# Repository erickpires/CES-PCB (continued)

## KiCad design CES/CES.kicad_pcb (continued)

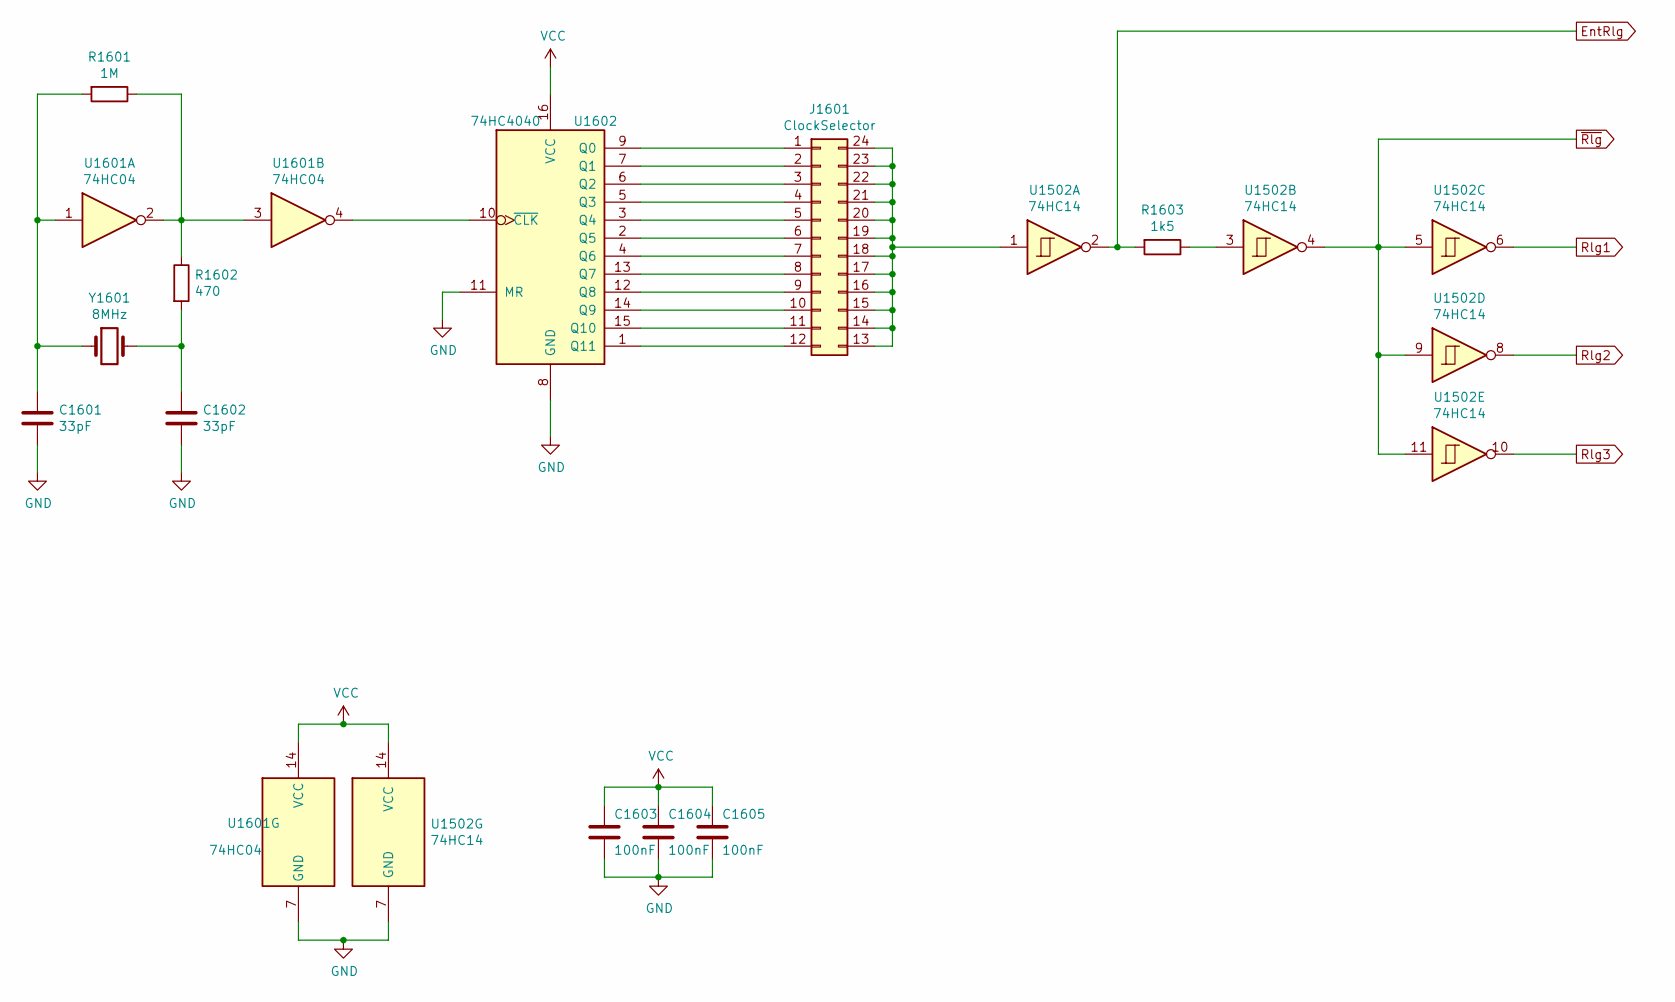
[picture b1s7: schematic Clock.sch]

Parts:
C1601, C1602: 33pF; CP_Radial_D5.0mm_P2.50mm
C1603, C1604, C1605: 100nF; CP_Radial_D5.0mm_P2.50mm
J1601: ClockSelector; PinHeader_2x12_P2.54mm_Vertical
R1601: 1M; R_Axial_DIN0204_L3.6mm_D1.6mm_P1.90mm_Vertical
R1602: 470; R_Axial_DIN0204_L3.6mm_D1.6mm_P1.90mm_Vertical
R1603: 1k5; R_Axial_DIN0204_L3.6mm_D1.6mm_P1.90mm_Vertical
U1502: 74HC14; DIP-14_W7.62mm
U1601: 74HC04; DIP-14_W7.62mm
U1602: 74HC4040; DIP-16_W7.62mm
Y1601: 8MHz; Crystal_HC33-U_Vertical

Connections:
EntRlg: R1603.2, U1502.2; also elsewhere on the board
GND: C1601.2, C1602.2, C1603.2, C1604.2, C1605.2, U1502.7 (GND), U1601.5, U1601.7 (GND), U1601.9, U1601.11, U1601.13, U1602.8 (GND), U1602.11 (MR); also elsewhere on the board
unnamed: C1601.1, R1601.2, U1601.1, Y1601.1
unnamed: C1602.1, R1602.2, Y1601.2
unnamed: J1601.1, U1602.9 (Q0)
unnamed: J1601.2, U1602.7 (Q1)
unnamed: J1601.3, U1602.6 (Q2)
unnamed: J1601.4, U1602.5 (Q3)
unnamed: J1601.5, U1602.3 (Q4)
unnamed: J1601.6, U1602.2 (Q5)
unnamed: J1601.7, U1602.4 (Q6)
unnamed: J1601.8, U1602.13 (Q7)
unnamed: J1601.9, U1602.12 (Q8)
unnamed: J1601.10, U1602.14 (Q9)
unnamed: J1601.11, U1602.15 (Q10)
unnamed: J1601.12, U1602.1 (Q11)
unnamed: J1601.13, J1601.14, J1601.15, J1601.16, J1601.17, J1601.18, J1601.19, J1601.20, J1601.21, J1601.22, J1601.23, J1601.24, U1502.1
unnamed: R1601.1, R1602.1, U1601.2, U1601.3
unnamed: R1603.1, U1502.3
unnamed: U1601.4, U1602.10 (~CLK)
Rlg1: U1502.6; also elsewhere on the board
Rlg2: U1502.8; also elsewhere on the board
Rlg3: U1502.10; also elsewhere on the board
VCC: C1603.1, C1604.1, C1605.1, U1502.14 (VCC), U1601.14 (VCC), U1602.16 (VCC); also elsewhere on the board
~Rlg: U1502.4, U1502.5, U1502.9, U1502.11; also elsewhere on the board

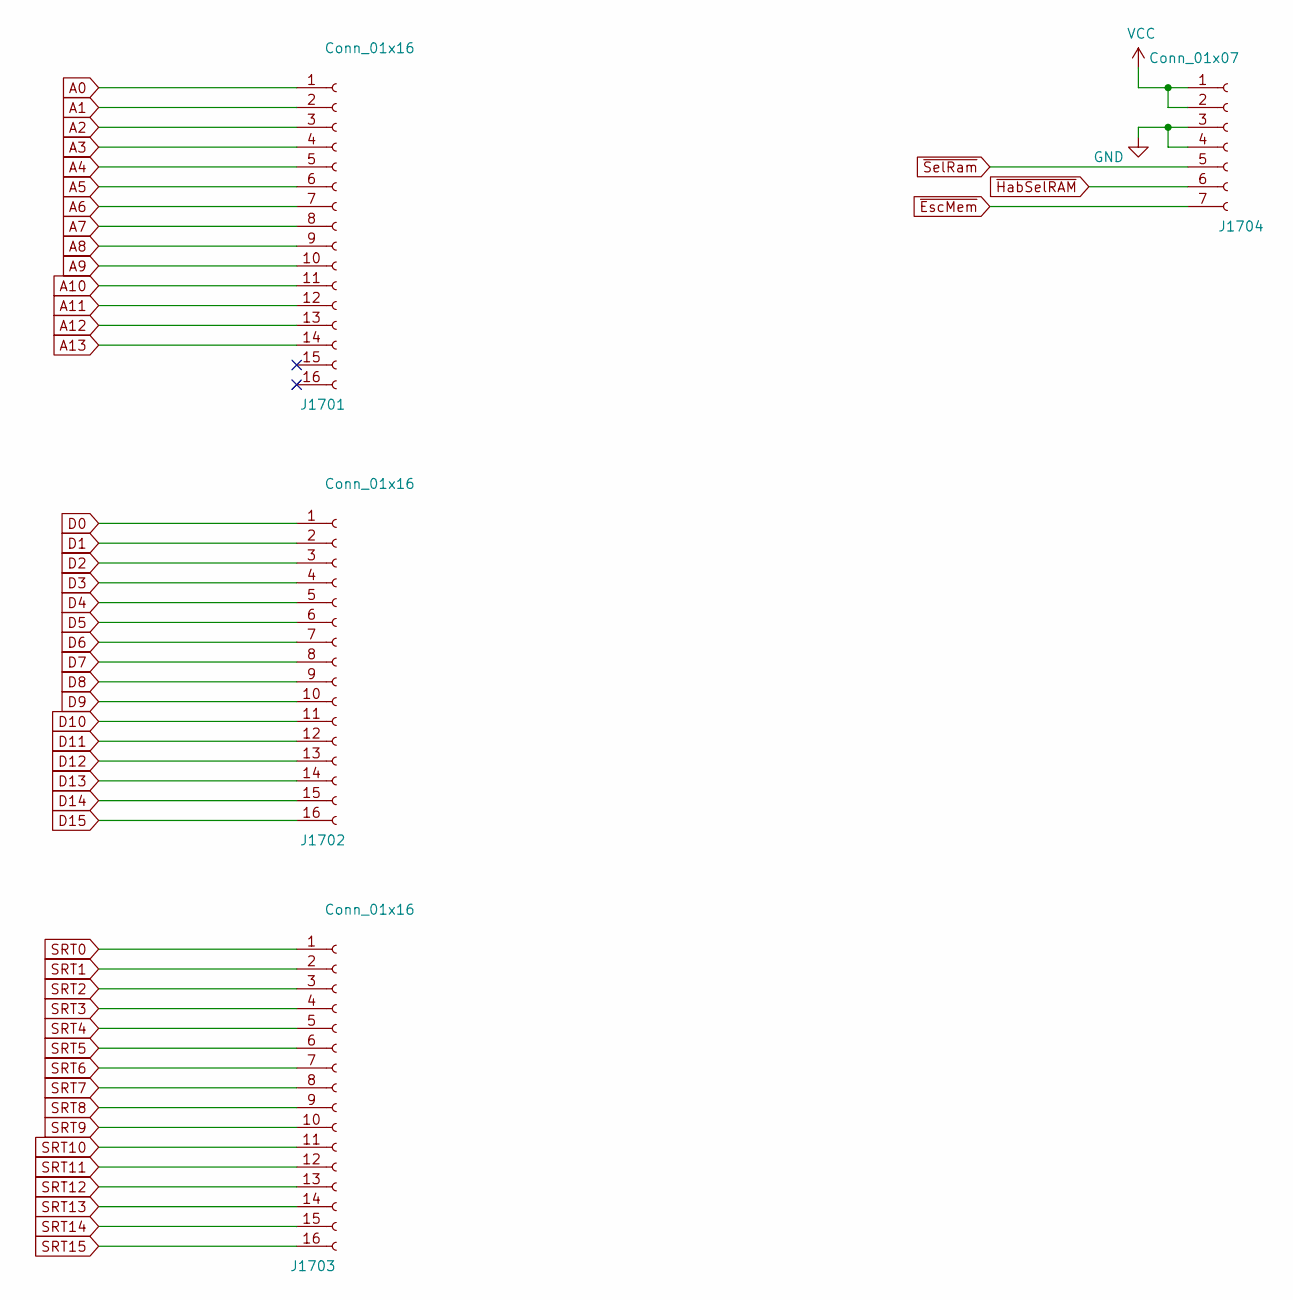
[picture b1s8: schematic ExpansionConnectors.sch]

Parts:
J1701, J1702, J1703: Conn_01x16; PinHeader_1x16_P2.54mm_Vertical
J1704: Conn_01x07; PinHeader_1x07_P2.54mm_Vertical

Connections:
A0: J1701.1; also elsewhere on the board
A1: J1701.2; also elsewhere on the board
A2: J1701.3; also elsewhere on the board
A3: J1701.4; also elsewhere on the board
A4: J1701.5; also elsewhere on the board
A5: J1701.6; also elsewhere on the board
A6: J1701.7; also elsewhere on the board
A7: J1701.8; also elsewhere on the board
A8: J1701.9; also elsewhere on the board
A9: J1701.10; also elsewhere on the board
A10: J1701.11; also elsewhere on the board
A11: J1701.12; also elsewhere on the board
A12: J1701.13; also elsewhere on the board
A13: J1701.14; also elsewhere on the board
D0: J1702.1; also elsewhere on the board
D1: J1702.2; also elsewhere on the board
D2: J1702.3; also elsewhere on the board
D3: J1702.4; also elsewhere on the board
D4: J1702.5; also elsewhere on the board
D5: J1702.6; also elsewhere on the board
D6: J1702.7; also elsewhere on the board
D7: J1702.8; also elsewhere on the board
D8: J1702.9; also elsewhere on the board
D9: J1702.10; also elsewhere on the board
D10: J1702.11; also elsewhere on the board
D11: J1702.12; also elsewhere on the board
D12: J1702.13; also elsewhere on the board
D13: J1702.14; also elsewhere on the board
D14: J1702.15; also elsewhere on the board
D15: J1702.16; also elsewhere on the board
GND: J1704.3, J1704.4; also elsewhere on the board
SRT0: J1703.1; also elsewhere on the board
SRT1: J1703.2; also elsewhere on the board
SRT2: J1703.3; also elsewhere on the board
SRT3: J1703.4; also elsewhere on the board
SRT4: J1703.5; also elsewhere on the board
SRT5: J1703.6; also elsewhere on the board
SRT6: J1703.7; also elsewhere on the board
SRT7: J1703.8; also elsewhere on the board
SRT8: J1703.9; also elsewhere on the board
SRT9: J1703.10; also elsewhere on the board
SRT10: J1703.11; also elsewhere on the board
SRT11: J1703.12; also elsewhere on the board
SRT12: J1703.13; also elsewhere on the board
SRT13: J1703.14; also elsewhere on the board
SRT14: J1703.15; also elsewhere on the board
SRT15: J1703.16; also elsewhere on the board
VCC: J1704.1, J1704.2; also elsewhere on the board
~EscMem: J1704.7; also elsewhere on the board
~HabSelRAM: J1704.6; also elsewhere on the board
~SelRam: J1704.5; also elsewhere on the board

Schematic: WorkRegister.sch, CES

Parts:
C401, C402, C403, C404, C405, C406: 100nF; C_Disc_D4.3mm_W1.9mm_P5.00mm
U401, U402, U403, U404: 74HC173; DIP-16_W7.62mm
U405, U406: 74HC244; DIP-20_W7.62mm

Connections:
GND: C401.2, C402.2, C403.2, C404.2, C405.2, C406.2, U401.1 (Oe1), U401.2 (Oe2), U401.8 (GND), U401.10 (E2), U401.15 (Mr), U402.1 (Oe1), U402.2 (Oe2), U402.8 (GND), U402.10 (E2), U402.15 (Mr), U403.1 (Oe1), U403.2 (Oe2), U403.8 (GND), U403.10 (E2), U403.15 (Mr), U404.1 (Oe1), U404.2 (Oe2), U404.8 (GND), U404.10 (E2), U404.15 (Mr), U405.10 (GND), U406.10 (GND); also elsewhere on the board
Rlg1: U401.7 (Cp), U402.7 (Cp), U403.7 (Cp), U404.7 (Cp); also elsewhere on the board
SRT0: U401.3 (Q0), U405.2 (1A0); also elsewhere on the board
SRT1: U401.4 (Q1), U405.4 (1A1); also elsewhere on the board
SRT2: U401.5 (Q2), U405.6 (1A2); also elsewhere on the board
SRT3: U401.6 (Q3), U405.8 (1A3); also elsewhere on the board
SRT4: U402.3 (Q0), U405.17 (2A0); also elsewhere on the board
SRT5: U402.4 (Q1), U405.15 (2A1); also elsewhere on the board
SRT6: U402.5 (Q2), U405.13 (2A2); also elsewhere on the board
SRT7: U402.6 (Q3), U405.11 (2A3); also elsewhere on the board
SRT8: U403.3 (Q0), U406.2 (1A0); also elsewhere on the board
SRT9: U403.4 (Q1), U406.4 (1A1); also elsewhere on the board
SRT10: U403.5 (Q2), U406.6 (1A2); also elsewhere on the board
SRT11: U403.6 (Q3), U406.8 (1A3); also elsewhere on the board
SRT12: U404.3 (Q0), U406.17 (2A0); also elsewhere on the board
SRT13: U404.4 (Q1), U406.15 (2A1); also elsewhere on the board
SRT14: U404.5 (Q2), U406.13 (2A2); also elsewhere on the board
SRT15: U404.6 (Q3), U406.11 (2A3); also elsewhere on the board
SS0: U401.14 (D0); also elsewhere on the board
SS1: U401.13 (D1); also elsewhere on the board
SS2: U401.12 (D2); also elsewhere on the board
SS3: U401.11 (D3); also elsewhere on the board
SS4: U402.14 (D0); also elsewhere on the board
SS5: U402.13 (D1); also elsewhere on the board
SS6: U402.12 (D2); also elsewhere on the board
SS7: U402.11 (D3); also elsewhere on the board
SS8: U403.14 (D0); also elsewhere on the board
SS9: U403.13 (D1); also elsewhere on the board
SS10: U403.12 (D2); also elsewhere on the board
SS11: U403.11 (D3); also elsewhere on the board
SS12: U404.14 (D0); also elsewhere on the board
SS13: U404.13 (D1); also elsewhere on the board
SS14: U404.12 (D2); also elsewhere on the board
SS15: U404.11 (D3); also elsewhere on the board
VCC: C401.1, C402.1, C403.1, C404.1, C405.1, C406.1, U401.16 (VCC), U402.16 (VCC), U403.16 (VCC), U404.16 (VCC), U405.20 (VCC), U406.20 (VCC); also elsewhere on the board
VDB0: U405.18 (1Y0); also elsewhere on the board
VDB1: U405.16 (1Y1); also elsewhere on the board
VDB2: U405.14 (1Y2); also elsewhere on the board
VDB3: U405.12 (1Y3); also elsewhere on the board
VDB4: U405.3 (2Y0); also elsewhere on the board
VDB5: U405.5 (2Y1); also elsewhere on the board
VDB6: U405.7 (2Y2); also elsewhere on the board
VDB7: U405.9 (2Y3); also elsewhere on the board
VDB8: U406.18 (1Y0); also elsewhere on the board
VDB9: U406.16 (1Y1); also elsewhere on the board
VDB10: U406.14 (1Y2); also elsewhere on the board
VDB11: U406.12 (1Y3); also elsewhere on the board
VDB12: U406.3 (2Y0); also elsewhere on the board
VDB13: U406.5 (2Y1); also elsewhere on the board
VDB14: U406.7 (2Y2); also elsewhere on the board
VDB15: U406.9 (2Y3); also elsewhere on the board
~EscM: U405.1 (1OE), U405.19 (2OE), U406.1 (1OE), U406.19 (2OE); also elsewhere on the board
~EscT: U401.9 (E1), U402.9 (E1), U403.9 (E1), U404.9 (E1); also elsewhere on the board

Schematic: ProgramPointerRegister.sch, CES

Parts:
C501, C502, C503, C504: 100nF; C_Disc_D4.3mm_W1.9mm_P5.00mm
C505: C; C_Disc_D4.3mm_W1.9mm_P5.00mm
R501: R; R_Axial_DIN0204_L3.6mm_D1.6mm_P1.90mm_Vertical
U501, U502, U503, U504: 74HC173; DIP-16_W7.62mm

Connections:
ESA0: U501.3 (Q0); also elsewhere on the board
ESA1: U501.4 (Q1); also elsewhere on the board
ESA2: U501.5 (Q2); also elsewhere on the board
ESA3: U501.6 (Q3); also elsewhere on the board
ESA4: U502.3 (Q0); also elsewhere on the board
ESA5: U502.4 (Q1); also elsewhere on the board
ESA6: U502.5 (Q2); also elsewhere on the board
ESA7: U502.6 (Q3); also elsewhere on the board
ESA8: U503.3 (Q0); also elsewhere on the board
ESA9: U503.4 (Q1); also elsewhere on the board
ESA10: U503.5 (Q2); also elsewhere on the board
ESA11: U503.6 (Q3); also elsewhere on the board
ESA12: U504.3 (Q0); also elsewhere on the board
ESA13: U504.4 (Q1); also elsewhere on the board
ESA14: U504.5 (Q2); also elsewhere on the board
ESA15: U504.6 (Q3); also elsewhere on the board
GND: C501.2, C502.2, C503.2, C504.2, R501.2, U501.2 (Oe2), U501.8 (GND), U501.10 (E2), U502.2 (Oe2), U502.8 (GND), U502.10 (E2), U503.2 (Oe2), U503.8 (GND), U503.10 (E2), U504.2 (Oe2), U504.8 (GND), U504.10 (E2); also elsewhere on the board
unnamed: C505.2, R501.1, U501.15 (Mr), U502.15 (Mr), U503.15 (Mr), U504.15 (Mr)
Rlg1: U501.7 (Cp), U502.7 (Cp), U503.7 (Cp), U504.7 (Cp); also elsewhere on the board
SS0: U501.14 (D0); also elsewhere on the board
SS1: U501.13 (D1); also elsewhere on the board
SS2: U501.12 (D2); also elsewhere on the board
SS3: U501.11 (D3); also elsewhere on the board
SS4: U502.14 (D0); also elsewhere on the board
SS5: U502.13 (D1); also elsewhere on the board
SS6: U502.12 (D2); also elsewhere on the board
SS7: U502.11 (D3); also elsewhere on the board
SS8: U503.14 (D0); also elsewhere on the board
SS9: U503.13 (D1); also elsewhere on the board
SS10: U503.12 (D2); also elsewhere on the board
SS11: U503.11 (D3); also elsewhere on the board
SS12: U504.14 (D0); also elsewhere on the board
SS13: U504.13 (D1); also elsewhere on the board
SS14: U504.12 (D2); also elsewhere on the board
SS15: U504.11 (D3); also elsewhere on the board
VCC: C501.1, C502.1, C503.1, C504.1, C505.1, U501.16 (VCC), U502.16 (VCC), U503.16 (VCC), U504.16 (VCC); also elsewhere on the board
~EscP: U501.9 (E1), U502.9 (E1), U503.9 (E1), U504.9 (E1); also elsewhere on the board
~SaiRP: U501.1 (Oe1), U502.1 (Oe1), U503.1 (Oe1), U504.1 (Oe1); also elsewhere on the board

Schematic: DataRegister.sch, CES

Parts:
C601, C602, C603, C604: 100nF; CP_Radial_D5.0mm_P2.50mm
U601: RD1; DIP-16_W7.62mm
U602: RD2; DIP-16_W7.62mm
U603: RD3; DIP-16_W7.62mm
U604: RD4; DIP-16_W7.62mm

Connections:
ESA0: U601.3 (Q0); also elsewhere on the board
ESA1: U601.4 (Q1); also elsewhere on the board
ESA2: U601.5 (Q2); also elsewhere on the board
ESA3: U601.6 (Q3); also elsewhere on the board
ESA4: U602.3 (Q0); also elsewhere on the board
ESA5: U602.4 (Q1); also elsewhere on the board
ESA6: U602.5 (Q2); also elsewhere on the board
ESA7: U602.6 (Q3); also elsewhere on the board
ESA8: U603.3 (Q0); also elsewhere on the board
ESA9: U603.4 (Q1); also elsewhere on the board
ESA10: U603.5 (Q2); also elsewhere on the board
ESA11: U603.6 (Q3); also elsewhere on the board
ESA12: U604.3 (Q0); also elsewhere on the board
ESA13: U604.4 (Q1); also elsewhere on the board
ESA14: U604.5 (Q2); also elsewhere on the board
ESA15: U604.6 (Q3); also elsewhere on the board
GND: C601.2, C602.2, C603.2, C604.2, U601.2 (Oe2), U601.8 (GND), U601.9 (E1), U601.10 (E2), U601.15 (Mr), U602.2 (Oe2), U602.8 (GND), U602.9 (E1), U602.10 (E2), U602.15 (Mr), U603.2 (Oe2), U603.8 (GND), U603.9 (E1), U603.10 (E2), U603.15 (Mr), U604.2 (Oe2), U604.8 (GND), U604.9 (E1), U604.10 (E2), U604.15 (Mr); also elsewhere on the board
Rlg2: U601.7 (Cp), U602.7 (Cp), U603.7 (Cp), U604.7 (Cp); also elsewhere on the board
VCC: C601.1, C602.1, C603.1, C604.1, U601.16 (VCC), U602.16 (VCC), U603.16 (VCC), U604.16 (VCC); also elsewhere on the board
VDB0: U601.14 (D0); also elsewhere on the board
VDB1: U601.13 (D1); also elsewhere on the board
VDB2: U601.12 (D2); also elsewhere on the board
VDB3: U601.11 (D3); also elsewhere on the board
VDB4: U602.14 (D0); also elsewhere on the board
VDB5: U602.13 (D1); also elsewhere on the board
VDB6: U602.12 (D2); also elsewhere on the board
VDB7: U602.11 (D3); also elsewhere on the board
VDB8: U603.14 (D0); also elsewhere on the board
VDB9: U603.13 (D1); also elsewhere on the board
VDB10: U603.12 (D2); also elsewhere on the board
VDB11: U603.11 (D3); also elsewhere on the board
VDB12: U604.14 (D0); also elsewhere on the board
VDB13: U604.13 (D1); also elsewhere on the board
VDB14: U604.12 (D2); also elsewhere on the board
VDB15: U604.11 (D3); also elsewhere on the board
~UltC: U601.1 (Oe1), U602.1 (Oe1), U603.1 (Oe1), U604.1 (Oe1); also elsewhere on the board

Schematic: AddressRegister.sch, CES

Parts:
C701, C702, C703, C704: 100nF; CP_Radial_D5.0mm_P2.50mm
U701: RE1; DIP-16_W7.62mm
U702: RE2; DIP-16_W7.62mm
U703: RE3; DIP-16_W7.62mm
U704: RE4; DIP-16_W7.62mm

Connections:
GND: C701.2, C702.2, C703.2, C704.2, U701.2 (Oe2), U701.8 (GND), U701.9 (E1), U701.10 (E2), U701.15 (Mr), U702.2 (Oe2), U702.8 (GND), U702.9 (E1), U702.10 (E2), U702.15 (Mr), U703.2 (Oe2), U703.8 (GND), U703.9 (E1), U703.10 (E2), U703.15 (Mr), U704.2 (Oe2), U704.8 (GND), U704.9 (E1), U704.10 (E2), U704.11 (D3), U704.12 (D2), U704.15 (Mr); also elsewhere on the board
Rlg2: U701.7 (Cp), U702.7 (Cp), U703.7 (Cp), U704.7 (Cp); also elsewhere on the board
SME0: U701.14 (D0); also elsewhere on the board
SME1: U701.13 (D1); also elsewhere on the board
SME2: U701.12 (D2); also elsewhere on the board
SME3: U701.11 (D3); also elsewhere on the board
SME4: U702.14 (D0); also elsewhere on the board
SME5: U702.13 (D1); also elsewhere on the board
SME6: U702.12 (D2); also elsewhere on the board
SME7: U702.11 (D3); also elsewhere on the board
SME8: U703.14 (D0); also elsewhere on the board
SME9: U703.13 (D1); also elsewhere on the board
SME10: U703.12 (D2); also elsewhere on the board
SME11: U703.11 (D3); also elsewhere on the board
SME12: U704.14 (D0); also elsewhere on the board
SME13: U704.13 (D1); also elsewhere on the board
VCC: C701.1, C702.1, C703.1, C704.1, U701.16 (VCC), U702.16 (VCC), U703.16 (VCC), U704.16 (VCC); also elsewhere on the board
VEB0: U701.3 (Q0); also elsewhere on the board
VEB1: U701.4 (Q1); also elsewhere on the board
VEB2: U701.5 (Q2); also elsewhere on the board
VEB3: U701.6 (Q3); also elsewhere on the board
VEB4: U702.3 (Q0); also elsewhere on the board
VEB5: U702.4 (Q1); also elsewhere on the board
VEB6: U702.5 (Q2); also elsewhere on the board
VEB7: U702.6 (Q3); also elsewhere on the board
VEB8: U703.3 (Q0); also elsewhere on the board
VEB9: U703.4 (Q1); also elsewhere on the board
VEB10: U703.5 (Q2); also elsewhere on the board
VEB11: U703.6 (Q3); also elsewhere on the board
VEB12: U704.3 (Q0); also elsewhere on the board
VEB13: U704.4 (Q1); also elsewhere on the board
~SaiRE: U701.1 (Oe1), U702.1 (Oe1), U703.1 (Oe1), U704.1 (Oe1); also elsewhere on the board

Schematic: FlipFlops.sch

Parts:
C901, C902, C903, C904: 100nF; C_Disc_D4.3mm_W1.9mm_P5.00mm
U901, U904: 74HC74; DIP-14_W7.62mm
U902: 74HC175; DIP-16_W7.62mm
U903: 74HC112; DIP-16_W7.62mm

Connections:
BotC0: U901.1 (~R); also elsewhere on the board
BotC1: U901.4 (~S); also elsewhere on the board
BotEscMem: U902.11 (~Q2); also elsewhere on the board
BotMem: U902.12 (D2); also elsewhere on the board
BotMudaP: U902.5 (D1); also elsewhere on the board
BotMudaT: U902.4 (D0); also elsewhere on the board
Est1: U901.9 (Q); also elsewhere on the board
GND: C901.2, C902.2, C903.2, C904.2, U901.7 (GND), U902.8 (GND), U903.8 (GND), U904.7 (GND); also elsewhere on the board
I0: U904.5 (Q); also elsewhere on the board
I1: U904.9 (Q); also elsewhere on the board
MudaP: U902.6 (~Q1); also elsewhere on the board
MudaT: U902.3 (~Q0); also elsewhere on the board
Para: U903.5 (Q); also elsewhere on the board
Parte: U902.15 (Q3), U903.2 (K), U903.11 (J); also elsewhere on the board
RC: U901.5 (Q); also elsewhere on the board
Rlg3: U901.11 (C), U902.9 (Cp); also elsewhere on the board
RlgRC: U901.3 (C); also elsewhere on the board
RlgRI: U904.3 (C), U904.11 (C); also elsewhere on the board
VCC: C901.1, C902.1, C903.1, C904.1, U901.10 (~S), U901.13 (~R), U901.14 (VCC), U902.1 (~Mr), U902.16 (VCC), U903.4 (~S), U903.10 (~S), U903.14 (~R), U903.15 (~R), U903.16 (VCC), U904.1 (~R), U904.4 (~S), U904.10 (~S), U904.13 (~R), U904.14 (VCC); also elsewhere on the board
VDB14: U904.2 (D); also elsewhere on the board
VDB15: U904.12 (D); also elsewhere on the board
VaiParar: U903.3 (J); also elsewhere on the board
VaiPartir: U902.13 (D3); also elsewhere on the board
VaiUm: U901.2 (D); also elsewhere on the board
~BotEscMem: U902.10 (Q2); also elsewhere on the board
~BotParteAtivo: U903.12 (K); also elsewhere on the board
~Est1: U901.8 (~Q); also elsewhere on the board
~I0: U904.6 (~Q); also elsewhere on the board
~I1: U904.8 (~Q); also elsewhere on the board
~Para: U903.6 (~Q); also elsewhere on the board
~Parte: U902.14 (~Q3); also elsewhere on the board
~Partiu: U903.7 (~Q); also elsewhere on the board
~RC: U901.6 (~Q); also elsewhere on the board
~Rlg: U903.1 (C), U903.13 (C); also elsewhere on the board
~UltC: U901.12 (D); also elsewhere on the board

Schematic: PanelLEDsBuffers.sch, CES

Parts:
C1301, C1302, C1303, C1304, C1305, C1306, C1307, C1308: 100nF; CP_Radial_D5.0mm_P2.50mm
J1301: PanelRT; PinHeader_1x16_P2.54mm_Vertical
J1302: PanelMem; PinHeader_1x16_P2.54mm_Vertical
J1303: PanelEnd; PinHeader_1x16_P2.54mm_Vertical
U1301, U1302, U1303, U1304, U1305, U1306, U1307, U1308: 74HC04; DIP-14_W7.62mm

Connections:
GND: C1301.2, C1302.2, C1303.2, C1304.2, C1305.2, C1306.2, C1307.2, C1308.2, U1301.7 (GND), U1302.7 (GND), U1303.7 (GND), U1304.7 (GND), U1305.7 (GND), U1306.7 (GND), U1307.7 (GND), U1308.7 (GND); also elsewhere on the board
unnamed: J1301.1, U1301.2
unnamed: J1301.2, U1301.4
unnamed: J1301.3, U1301.6
unnamed: J1301.4, U1301.8
unnamed: J1301.5, U1301.10
unnamed: J1301.6, U1301.12
unnamed: J1301.7, U1302.2
unnamed: J1301.8, U1302.4
unnamed: J1301.9, U1302.6
unnamed: J1301.10, U1302.8
unnamed: J1301.11, U1302.10
unnamed: J1301.12, U1302.12
unnamed: J1301.13, U1303.2
unnamed: J1301.14, U1303.4
unnamed: J1301.15, U1303.6
unnamed: J1301.16, U1303.8
unnamed: J1302.1, U1303.10
unnamed: J1302.2, U1303.12
unnamed: J1302.3, U1304.2
unnamed: J1302.4, U1304.4
unnamed: J1302.5, U1304.6
unnamed: J1302.6, U1304.8
unnamed: J1302.7, U1304.10
unnamed: J1302.8, U1304.12
unnamed: J1302.9, U1305.2
unnamed: J1302.10, U1305.4
unnamed: J1302.11, U1305.6
unnamed: J1302.12, U1305.8
unnamed: J1302.13, U1305.10
unnamed: J1302.14, U1305.12
unnamed: J1302.15, U1306.2
unnamed: J1302.16, U1306.4
unnamed: J1303.1, U1306.6
unnamed: J1303.2, U1306.8
unnamed: J1303.3, U1306.10
unnamed: J1303.4, U1306.12
unnamed: J1303.5, U1307.2
unnamed: J1303.6, U1307.4
unnamed: J1303.7, U1307.6
unnamed: J1303.8, U1307.8
unnamed: J1303.9, U1307.10
unnamed: J1303.10, U1307.12
unnamed: J1303.11, U1308.2
unnamed: J1303.12, U1308.4
unnamed: J1303.13, U1308.6
unnamed: J1303.14, U1308.8
unnamed: J1303.15, U1308.10
unnamed: J1303.16, U1308.12
Para: U1308.13; also elsewhere on the board
SRT0: U1301.1; also elsewhere on the board
SRT1: U1301.3; also elsewhere on the board
SRT2: U1301.5; also elsewhere on the board
SRT3: U1301.9; also elsewhere on the board
SRT4: U1301.11; also elsewhere on the board
SRT5: U1301.13; also elsewhere on the board
SRT6: U1302.1; also elsewhere on the board
SRT7: U1302.3; also elsewhere on the board
SRT8: U1302.5; also elsewhere on the board
SRT9: U1302.9; also elsewhere on the board
SRT10: U1302.11; also elsewhere on the board
SRT11: U1302.13; also elsewhere on the board
SRT12: U1303.1; also elsewhere on the board
SRT13: U1303.3; also elsewhere on the board
SRT14: U1303.5; also elsewhere on the board
SRT15: U1303.9; also elsewhere on the board
SS0: U1306.5; also elsewhere on the board
SS1: U1306.9; also elsewhere on the board
SS2: U1306.11; also elsewhere on the board
SS3: U1306.13; also elsewhere on the board
SS4: U1307.1; also elsewhere on the board
SS5: U1307.3; also elsewhere on the board
SS6: U1307.5; also elsewhere on the board
SS7: U1307.9; also elsewhere on the board
SS8: U1307.11; also elsewhere on the board
SS9: U1307.13; also elsewhere on the board
SS10: U1308.1; also elsewhere on the board
SS11: U1308.3; also elsewhere on the board
SS12: U1308.5; also elsewhere on the board
SS13: U1308.9; also elsewhere on the board
VCC: C1301.1, C1302.1, C1303.1, C1304.1, C1305.1, C1306.1, C1307.1, C1308.1, U1301.14 (VCC), U1302.14 (VCC), U1303.14 (VCC), U1304.14 (VCC), U1305.14 (VCC), U1306.14 (VCC), U1307.14 (VCC), U1308.14 (VCC); also elsewhere on the board
VDB0: U1303.11; also elsewhere on the board
VDB1: U1303.13; also elsewhere on the board
VDB2: U1304.1; also elsewhere on the board
VDB3: U1304.3; also elsewhere on the board
VDB4: U1304.5; also elsewhere on the board
VDB5: U1304.9; also elsewhere on the board
VDB6: U1304.11; also elsewhere on the board
VDB7: U1304.13; also elsewhere on the board
VDB8: U1305.1; also elsewhere on the board
VDB9: U1305.3; also elsewhere on the board
VDB10: U1305.5; also elsewhere on the board
VDB11: U1305.9; also elsewhere on the board
VDB12: U1305.11; also elsewhere on the board
VDB13: U1305.13; also elsewhere on the board
VDB14: U1306.1; also elsewhere on the board
VDB15: U1306.3; also elsewhere on the board
~RC: U1308.11; also elsewhere on the board

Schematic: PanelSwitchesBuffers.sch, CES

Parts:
C1401, C1402, C1403, C1404, C1405, C1406: 100nF; CP_Radial_D5.0mm_P2.50mm
J1401: InputDataSwitches; PinHeader_1x16_P2.54mm_Vertical
J1402: InputAddressSwitches; PinHeader_1x16_P2.54mm_Vertical
U1401: BD1; DIP-20_W7.62mm
U1402: BS1; DIP-20_W7.62mm
U1403: BD2; DIP-20_W7.62mm
U1404: BS2; DIP-20_W7.62mm
U1405: BE1; DIP-20_W7.62mm
U1406: BE2; DIP-20_W7.62mm

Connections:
ESA0: U1402.18 (1Y0); also elsewhere on the board
ESA1: U1402.16 (1Y1); also elsewhere on the board
ESA2: U1402.14 (1Y2); also elsewhere on the board
ESA3: U1402.12 (1Y3); also elsewhere on the board
ESA4: U1402.3 (2Y0); also elsewhere on the board
ESA5: U1402.5 (2Y1); also elsewhere on the board
ESA6: U1402.7 (2Y2); also elsewhere on the board
ESA7: U1402.9 (2Y3); also elsewhere on the board
ESA8: U1404.18 (1Y0); also elsewhere on the board
ESA9: U1404.16 (1Y1); also elsewhere on the board
ESA10: U1404.14 (1Y2); also elsewhere on the board
ESA11: U1404.12 (1Y3); also elsewhere on the board
ESA12: U1404.3 (2Y0); also elsewhere on the board
ESA13: U1404.5 (2Y1); also elsewhere on the board
ESA14: U1404.7 (2Y2); also elsewhere on the board
ESA15: U1404.9 (2Y3); also elsewhere on the board
GND: C1401.2, C1402.2, C1403.2, C1404.2, C1405.2, C1406.2, U1401.10 (GND), U1402.10 (GND), U1403.10 (GND), U1404.10 (GND), U1405.10 (GND), U1406.10 (GND), U1406.11 (2A3), U1406.13 (2A2); also elsewhere on the board
unnamed: J1401.1, U1401.2 (1A0), U1402.2 (1A0)
unnamed: J1401.2, U1401.4 (1A1), U1402.4 (1A1)
unnamed: J1401.3, U1401.6 (1A2), U1402.6 (1A2)
unnamed: J1401.4, U1401.8 (1A3), U1402.8 (1A3)
unnamed: J1401.5, U1401.17 (2A0), U1402.17 (2A0)
unnamed: J1401.6, U1401.15 (2A1), U1402.15 (2A1)
unnamed: J1401.7, U1401.13 (2A2), U1402.13 (2A2)
unnamed: J1401.8, U1401.11 (2A3), U1402.11 (2A3)
unnamed: J1401.9, U1403.2 (1A0), U1404.2 (1A0)
unnamed: J1401.10, U1403.4 (1A1), U1404.4 (1A1)
unnamed: J1401.11, U1403.6 (1A2), U1404.6 (1A2)
unnamed: J1401.12, U1403.8 (1A3), U1404.8 (1A3)
unnamed: J1401.13, U1403.17 (2A0), U1404.17 (2A0)
unnamed: J1401.14, U1403.15 (2A1), U1404.15 (2A1)
unnamed: J1401.15, U1403.13 (2A2), U1404.13 (2A2)
unnamed: J1401.16, U1403.11 (2A3), U1404.11 (2A3)
unnamed: J1402.1, U1405.2 (1A0)
unnamed: J1402.2, U1405.4 (1A1)
unnamed: J1402.3, U1405.6 (1A2)
unnamed: J1402.4, U1405.8 (1A3)
unnamed: J1402.5, U1405.17 (2A0)
unnamed: J1402.6, U1405.15 (2A1)
unnamed: J1402.7, U1405.13 (2A2)
unnamed: J1402.8, U1405.11 (2A3)
unnamed: J1402.9, U1406.2 (1A0)
unnamed: J1402.10, U1406.4 (1A1)
unnamed: J1402.11, U1406.6 (1A2)
unnamed: J1402.12, U1406.8 (1A3)
unnamed: J1402.13, U1406.17 (2A0)
unnamed: J1402.14, U1406.15 (2A1)
VCC: C1401.1, C1402.1, C1403.1, C1404.1, C1405.1, C1406.1, U1401.20 (VCC), U1402.20 (VCC), U1403.20 (VCC), U1404.20 (VCC), U1405.20 (VCC), U1406.20 (VCC); also elsewhere on the board
VDB0: U1401.18 (1Y0); also elsewhere on the board
VDB1: U1401.16 (1Y1); also elsewhere on the board
VDB2: U1401.14 (1Y2); also elsewhere on the board
VDB3: U1401.12 (1Y3); also elsewhere on the board
VDB4: U1401.3 (2Y0); also elsewhere on the board
VDB5: U1401.5 (2Y1); also elsewhere on the board
VDB6: U1401.7 (2Y2); also elsewhere on the board
VDB7: U1401.9 (2Y3); also elsewhere on the board
VDB8: U1403.18 (1Y0); also elsewhere on the board
VDB9: U1403.16 (1Y1); also elsewhere on the board
VDB10: U1403.14 (1Y2); also elsewhere on the board
VDB11: U1403.12 (1Y3); also elsewhere on the board
VDB12: U1403.3 (2Y0); also elsewhere on the board
VDB13: U1403.5 (2Y1); also elsewhere on the board
VDB14: U1403.7 (2Y2); also elsewhere on the board
VDB15: U1403.9 (2Y3); also elsewhere on the board
VEB0: U1405.18 (1Y0); also elsewhere on the board
VEB1: U1405.16 (1Y1); also elsewhere on the board
VEB2: U1405.14 (1Y2); also elsewhere on the board
VEB3: U1405.12 (1Y3); also elsewhere on the board
VEB4: U1405.3 (2Y0); also elsewhere on the board
VEB5: U1405.5 (2Y1); also elsewhere on the board
VEB6: U1405.7 (2Y2); also elsewhere on the board
VEB7: U1405.9 (2Y3); also elsewhere on the board
VEB8: U1406.18 (1Y0); also elsewhere on the board
VEB9: U1406.16 (1Y1); also elsewhere on the board
VEB10: U1406.14 (1Y2); also elsewhere on the board
VEB11: U1406.12 (1Y3); also elsewhere on the board
VEB12: U1406.3 (2Y0); also elsewhere on the board
VEB13: U1406.5 (2Y1); also elsewhere on the board
~SaiBD: U1401.1 (1OE), U1401.19 (2OE), U1403.1 (1OE), U1403.19 (2OE); also elsewhere on the board
~SaiBE: U1405.1 (1OE), U1405.19 (2OE), U1406.1 (1OE), U1406.19 (2OE); also elsewhere on the board
~SaiBS: U1402.1 (1OE), U1402.19 (2OE), U1404.1 (1OE), U1404.19 (2OE); also elsewhere on the board

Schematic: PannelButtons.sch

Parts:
C1501: 100nF; CP_Radial_D5.0mm_P2.50mm
J1501: PannelButtonsConnector; PinHeader_1x08_P2.54mm_Vertical
R1501, R1502, R1503, R1504, R1505, R1506, R1507, R1508: 1k5; R_Axial_DIN0204_L3.6mm_D1.6mm_P1.90mm_Vertical
U1501: 74HC00; DIP-14_W7.62mm
U1502: 74HC14; DIP-14_W7.62mm

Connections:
/PannelInterface/PannelButtons/_BotPartePolo1: J1501.2, R1507.2, U1501.1
/PannelInterface/PannelButtons/_BotPartePolo2: J1501.3, R1508.2, U1501.4
/PannelInterface/PannelButtons/~BotParte: U1501.3, U1501.5, U1502.13
BotC0: J1501.8, R1506.2; also elsewhere on the board
BotC1: J1501.7, R1505.2; also elsewhere on the board
BotMem: J1501.6, R1504.2; also elsewhere on the board
BotMudaP: J1501.4, R1502.2; also elsewhere on the board
BotMudaT: J1501.5, R1503.2; also elsewhere on the board
BotParteAtivo: U1502.12; also elsewhere on the board
GND: C1501.2, U1501.7 (GND), U1501.9, U1501.10, U1501.12, U1501.13; also elsewhere on the board
unnamed: U1501.2, U1501.6
VCC: C1501.1, R1501.1, R1502.1, R1503.1, R1504.1, R1505.1, R1506.1, R1507.1, R1508.1, U1501.14 (VCC); also elsewhere on the board
~IntPara: J1501.1, R1501.2; also elsewhere on the board

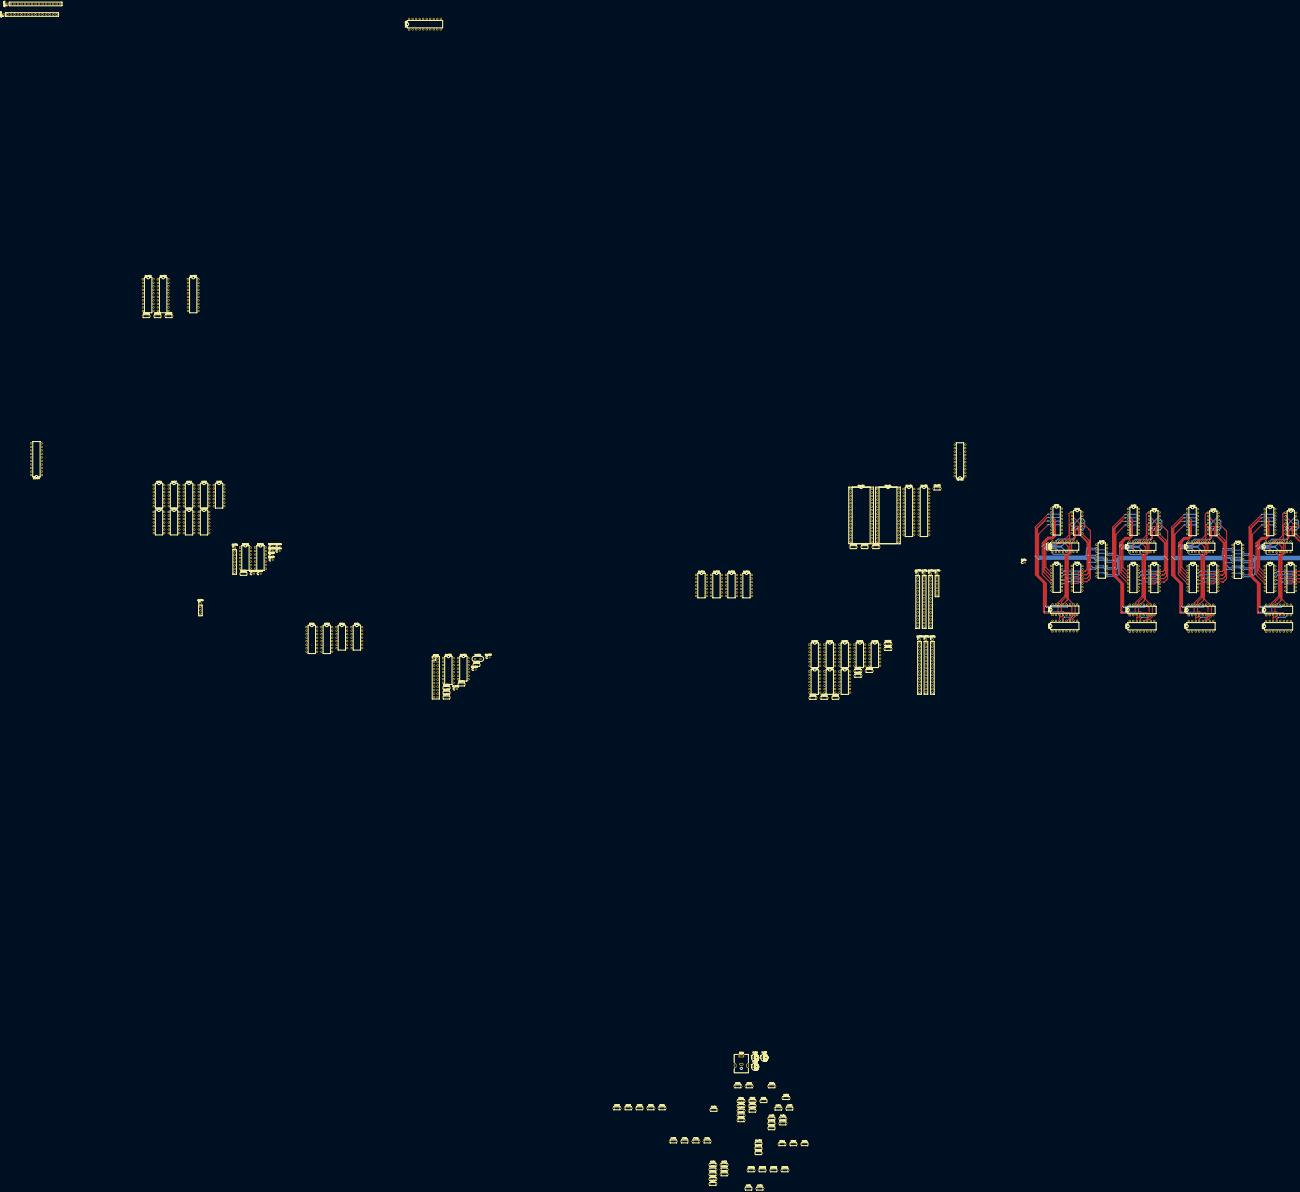
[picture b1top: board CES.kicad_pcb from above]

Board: 2 copper layers, 170 parts (0 on the bottom side), 310 nets.

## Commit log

2021-04-24 Registers
2021-04-24 Adding License
2021-04-24 Sheets information
2021-04-25 Address decoding. Clock. Pannel buttons
2021-04-25 Adding 74HC versions of 74LS chips
2021-04-25 ExpansionConnectors
2021-04-26 Control Unit
2021-04-26 Correcting ERC issues
2021-04-26 Assigning footprints and generating netlist
2021-04-29 Correcting footprints errors
2021-05-05 Starting PCB design
2021-05-06 Simplifying tracks
2021-05-06 Minimizing used space
2021-05-06 Wiring BT
2021-05-06 Crtl+C Crlt+V
2021-05-07 All adders, registers and multiplexers in place
